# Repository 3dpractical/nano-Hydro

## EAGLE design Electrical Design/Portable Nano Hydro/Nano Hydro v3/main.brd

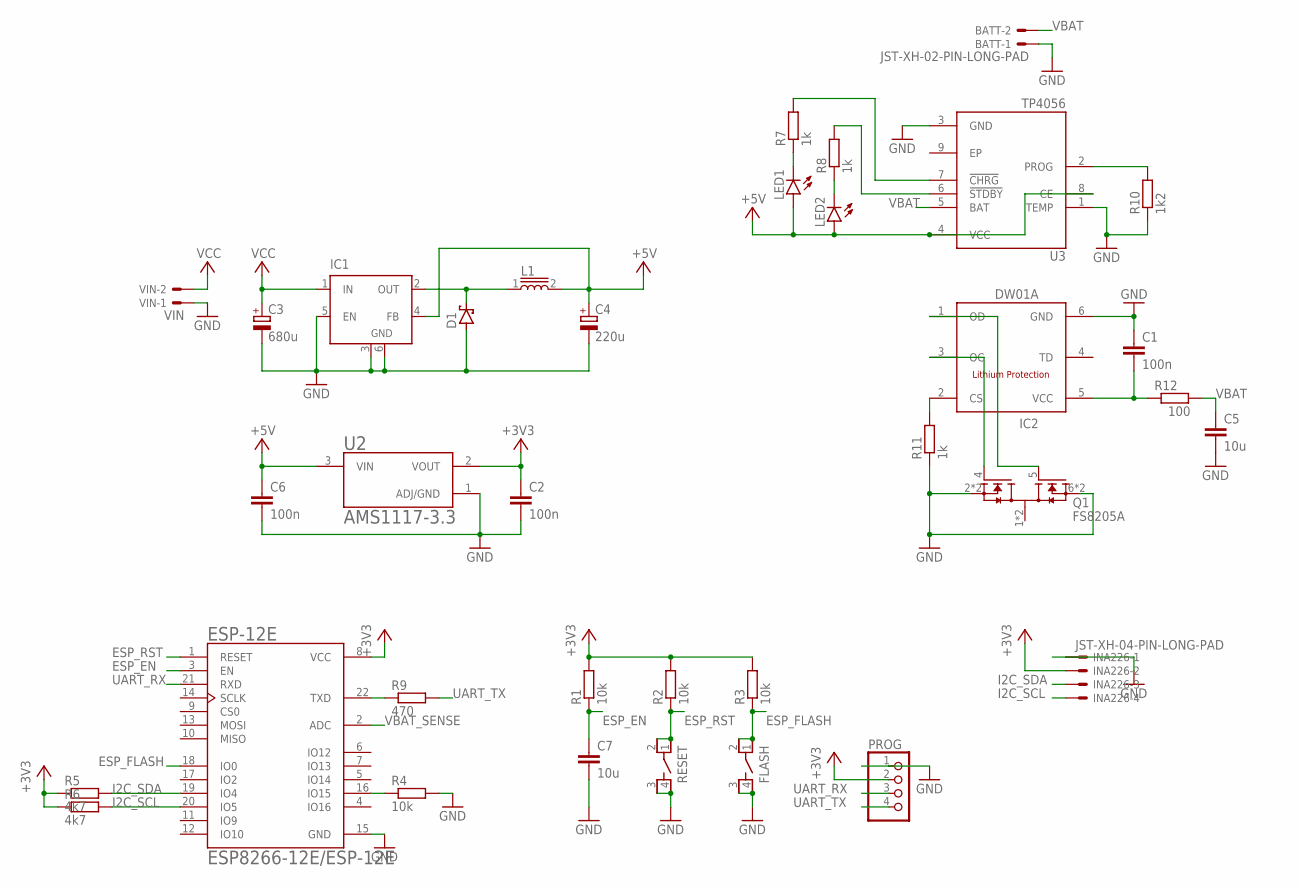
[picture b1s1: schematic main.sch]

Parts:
BATT: JST-XH-02-PIN-LONG-PAD; JST-XH-02-PACKAGE-LONG-PAD
C1, C2, C6: 100n; C0805
C3: 680u; 150CLZ-1010
C4: 220u; 150CLZ-0810
C5, C7: 10u; C0805
D1: SCHOTTKY-DIODESMD; SMB
ESP-12E: ESP8266-12E/ESP-12E; XCVR_ESP8266-12E/ESP-12E
FLASH: PTS810_SJM_250_SMTR_LFS; SW_PTS810_SJM_250_SMTR_LFS
IC1: LM2596S; TO263-5
IC2: DW01A; SOT23-6
INA226: JST-XH-04-PIN-LONG-PAD; JST-XH-04-PACKAGE-LONG-PAD
L1: 33uH; INDM1250X1250X600
LED1, LED2: LEDCHIPLED_0805; CHIPLED_0805
PROG: PINHD-1X4; 1X04
Q1: FS8205A; SOP65P640X120-8N
R1, R2, R3, R4: 10k; R0805
R5, R6: 4k7; R0805
R7, R8, R11: 1k; R0805
R9: 470; R0805
R10: 1k2; R0805
R12: 100; R0805
RESET: PTS810_SJM_250_SMTR_LFS; SW_PTS810_SJM_250_SMTR_LFS
U2: AMS1117-3.3; SOT229P700X180-4N
U3: TP4056; SOP127P600X175-9N
VIN: VIN; JST-XH-02-PACKAGE-LONG-PAD

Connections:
+3V3: C2.1, ESP-12E.8 (VCC), INA226.2, PROG.2, R1.2, R2.2, R3.2, R5.1, R6.1, U2.2 (VOUT)
+5V: C4.+, C6.1, IC1.4 (FB), L1.2, LED1.A, LED2.A, U2.3 (VIN), U3.4 (VCC), U3.8 (CE)
ESP_EN: C7.1, ESP-12E.3 (EN), R1.1
ESP_FLASH: ESP-12E.18 (IO0), FLASH.1, FLASH.2, R3.1
ESP_RST: ESP-12E.1 (RESET), R2.1, RESET.1, RESET.2
GND: BATT.1, C1.1, C2.2, C3.-, C4.-, C5.2, C6.2, C7.2, D1.A, ESP-12E.15 (GND), FLASH.3, FLASH.4, IC1.3 (GND), IC1.5 (EN), IC1.6 (GND), IC2.6 (GND), INA226.1, PROG.1, Q1.2 (S1), Q1.3 (S1), Q1.6 (S2), Q1.7 (S2), R4.2, R10.1, R11.1, RESET.3, RESET.4, U2.1 (ADJ/GND), U3.1 (TEMP), U3.3 (GND), VIN.1
I2C_SCL: ESP-12E.20 (IO5), INA226.4, R6.2
I2C_SDA: ESP-12E.19 (IO4), INA226.3, R5.2
unnamed: ESP-12E.22 (TXD), R9.1
unnamed: ESP-12E.16 (IO15), R4.1
unnamed: LED1.C, R7.1
unnamed: LED2.C, R8.1
unnamed: D1.C, IC1.2 (OUT), L1.1
unnamed: R8.2, U3.6 (!STDBY)
unnamed: R7.2, U3.7 (!CHRG)
unnamed: R10.2, U3.2 (PROG)
unnamed: IC2.2 (CS), R11.2
unnamed: C1.2, IC2.5 (VCC), R12.1
unnamed: IC2.3 (OC), Q1.4 (G1)
unnamed: IC2.1 (OD), Q1.5 (G2)
UART_RX: ESP-12E.21 (RXD), PROG.3
UART_TX: PROG.4, R9.2
VBAT: BATT.2, C5.1, R12.2, U3.5 (BAT)
VBAT_SENSE: ESP-12E.2 (ADC)
VCC: C3.+, IC1.1 (IN), VIN.2

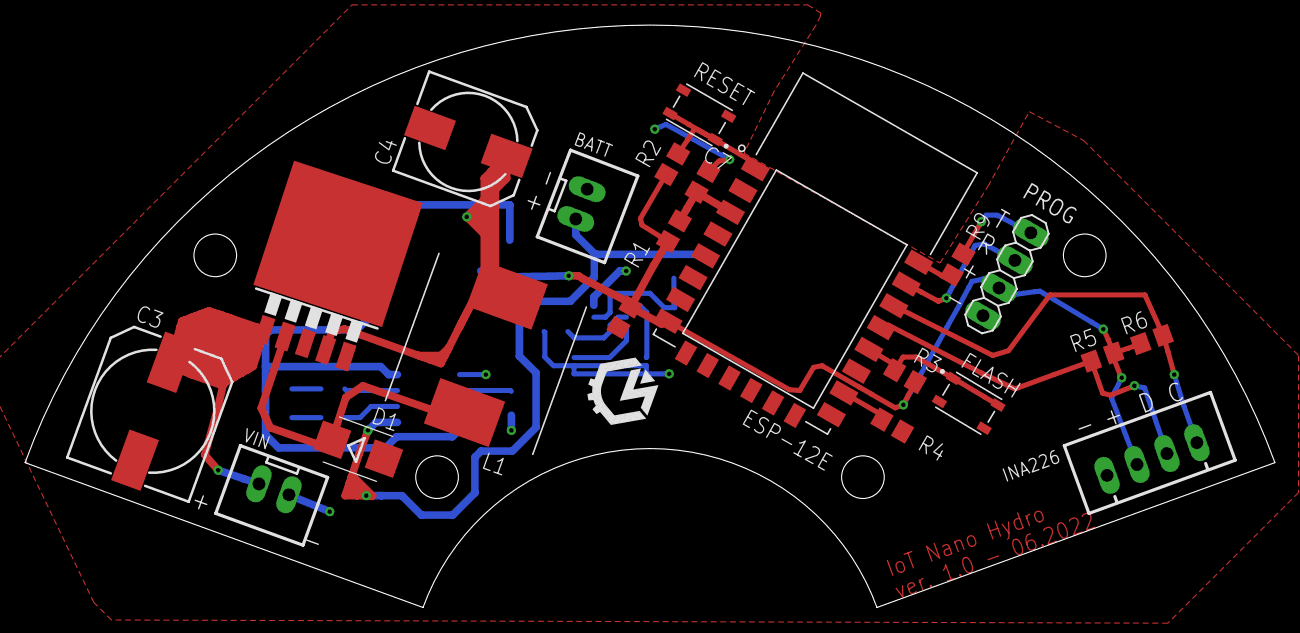
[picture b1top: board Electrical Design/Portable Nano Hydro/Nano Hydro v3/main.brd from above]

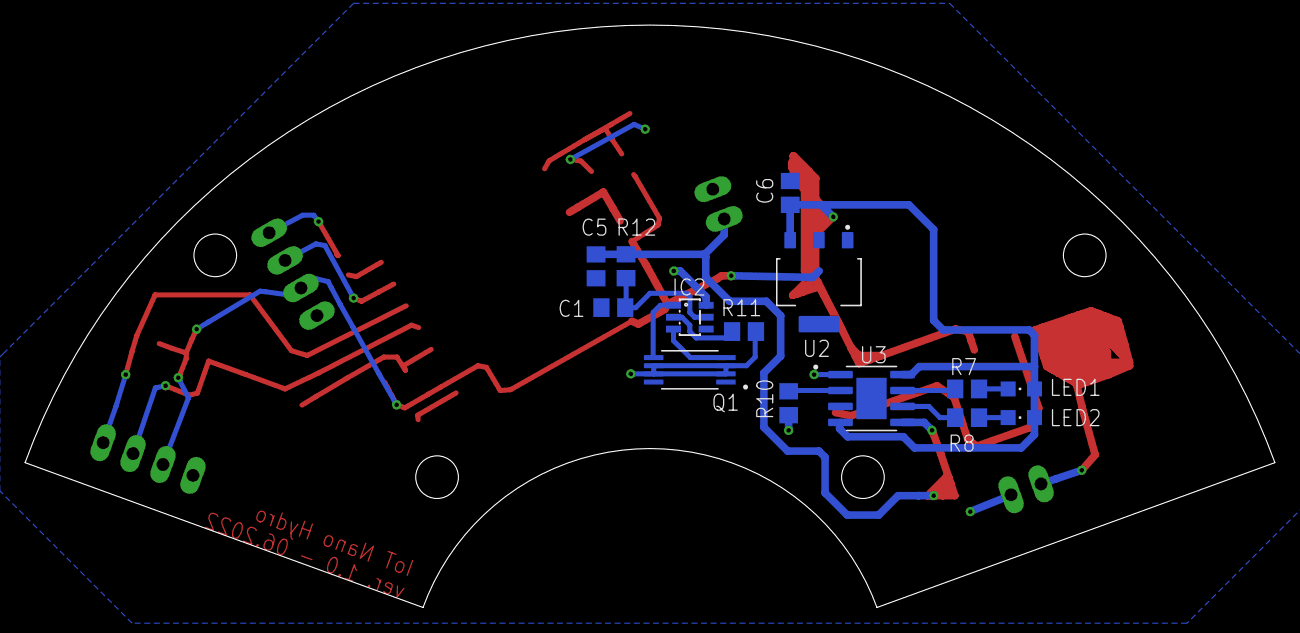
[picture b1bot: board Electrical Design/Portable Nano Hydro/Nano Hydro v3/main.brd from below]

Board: 2 copper layers, 99.6 x 46.4 mm, 35 parts (14 on the bottom side), 24 nets.

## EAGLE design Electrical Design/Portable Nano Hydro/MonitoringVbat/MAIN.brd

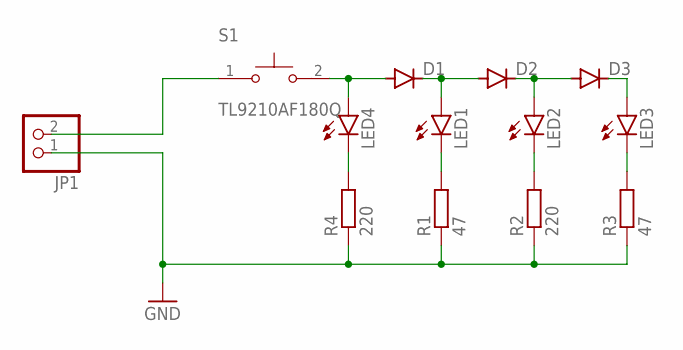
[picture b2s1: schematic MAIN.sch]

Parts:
D1, D2, D3: DIODE-SMB; SMB
JP1: PINHD-1X2; 1X02
LED1, LED2, LED3, LED4: LED5MM
R1, R3: 47; R0805
R2, R4: 220; R0805
S1: TL9210AF180Q; SW_TL9210AF180Q

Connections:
GND: JP1.1, R1.1, R2.1, R3.1, R4.1
unnamed: D1.C, D2.A, LED1.A
unnamed: D2.C, D3.A, LED2.A
unnamed: D3.C, LED3.A
unnamed: D1.A, LED4.A, S1.2
unnamed: LED4.K (C), R4.2
unnamed: LED1.K (C), R1.2
unnamed: LED2.K (C), R2.2
unnamed: LED3.K (C), R3.2
unnamed: JP1.2, S1.1

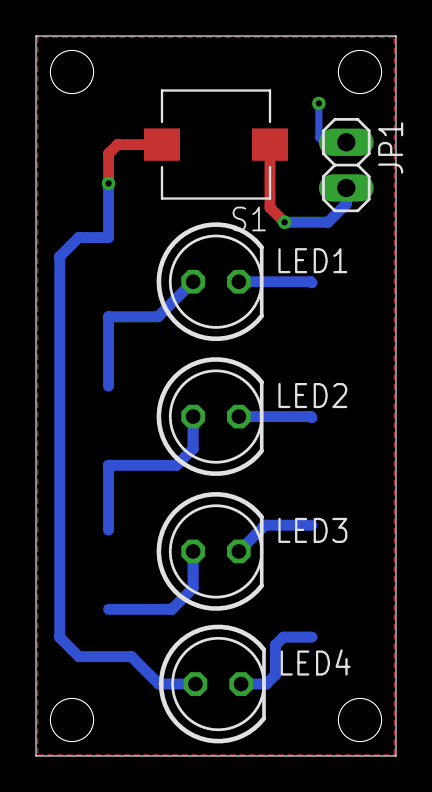
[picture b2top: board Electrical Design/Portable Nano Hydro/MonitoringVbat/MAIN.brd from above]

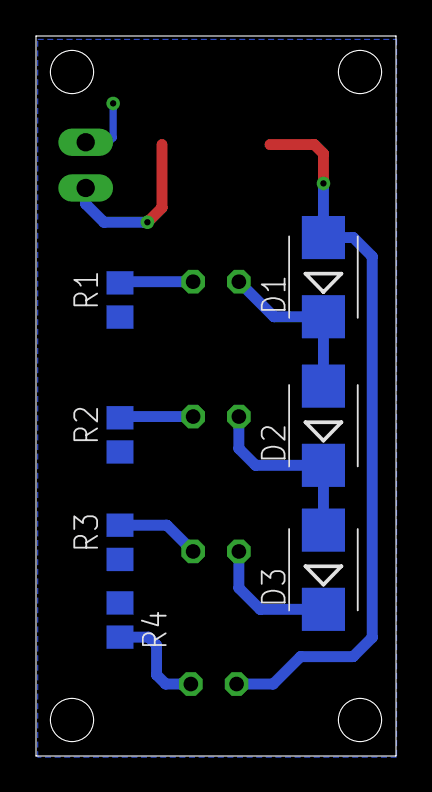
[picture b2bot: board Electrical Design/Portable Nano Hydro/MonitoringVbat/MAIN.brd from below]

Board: 2 copper layers, 20.0 x 40.0 mm, 13 parts (7 on the bottom side), 10 nets.

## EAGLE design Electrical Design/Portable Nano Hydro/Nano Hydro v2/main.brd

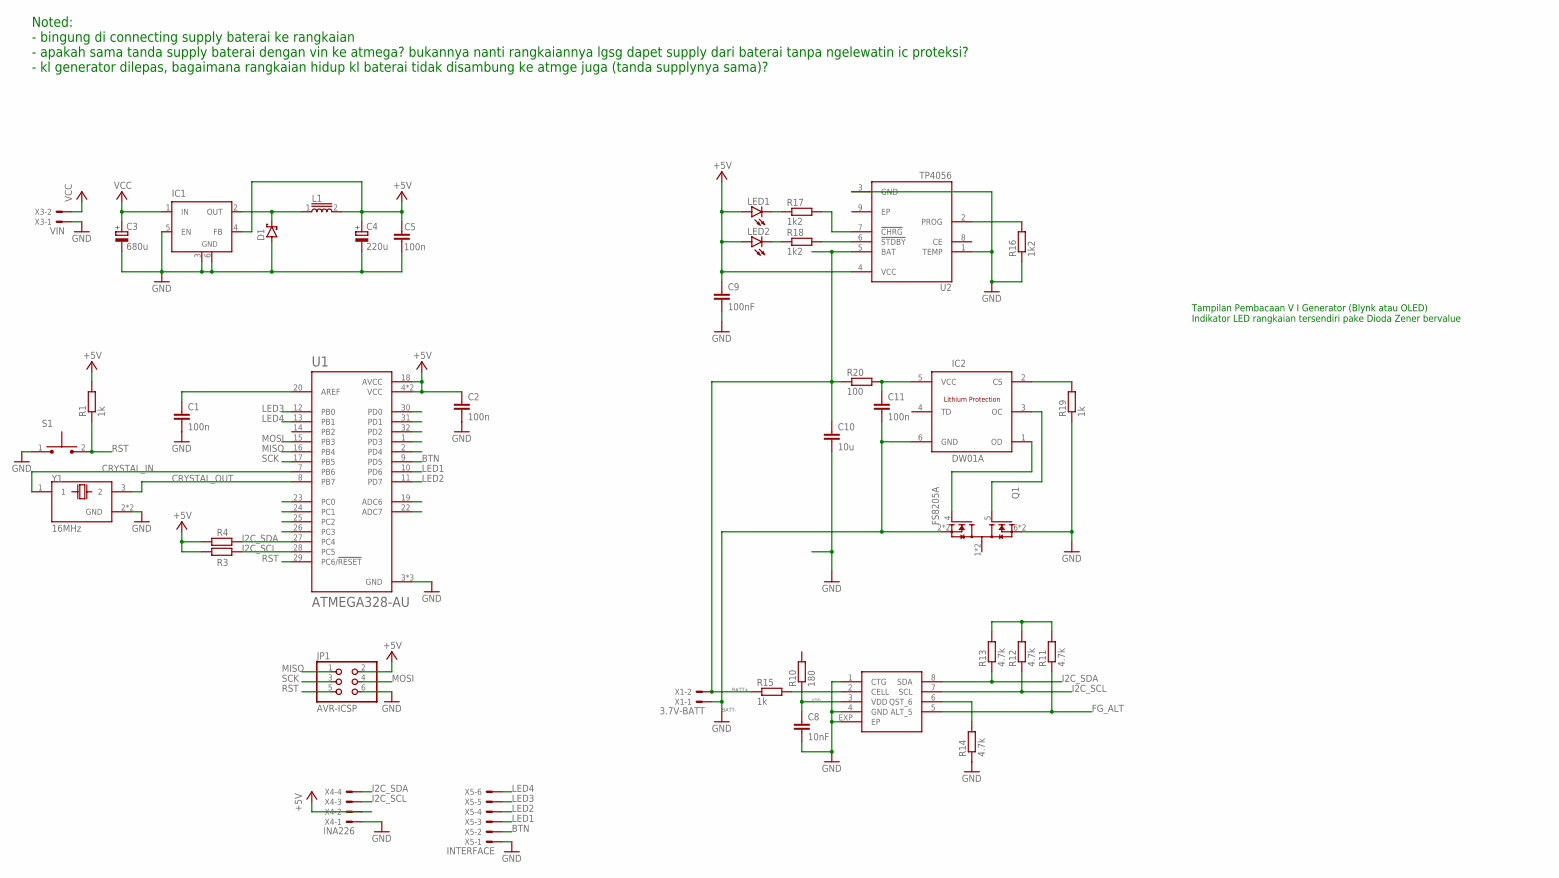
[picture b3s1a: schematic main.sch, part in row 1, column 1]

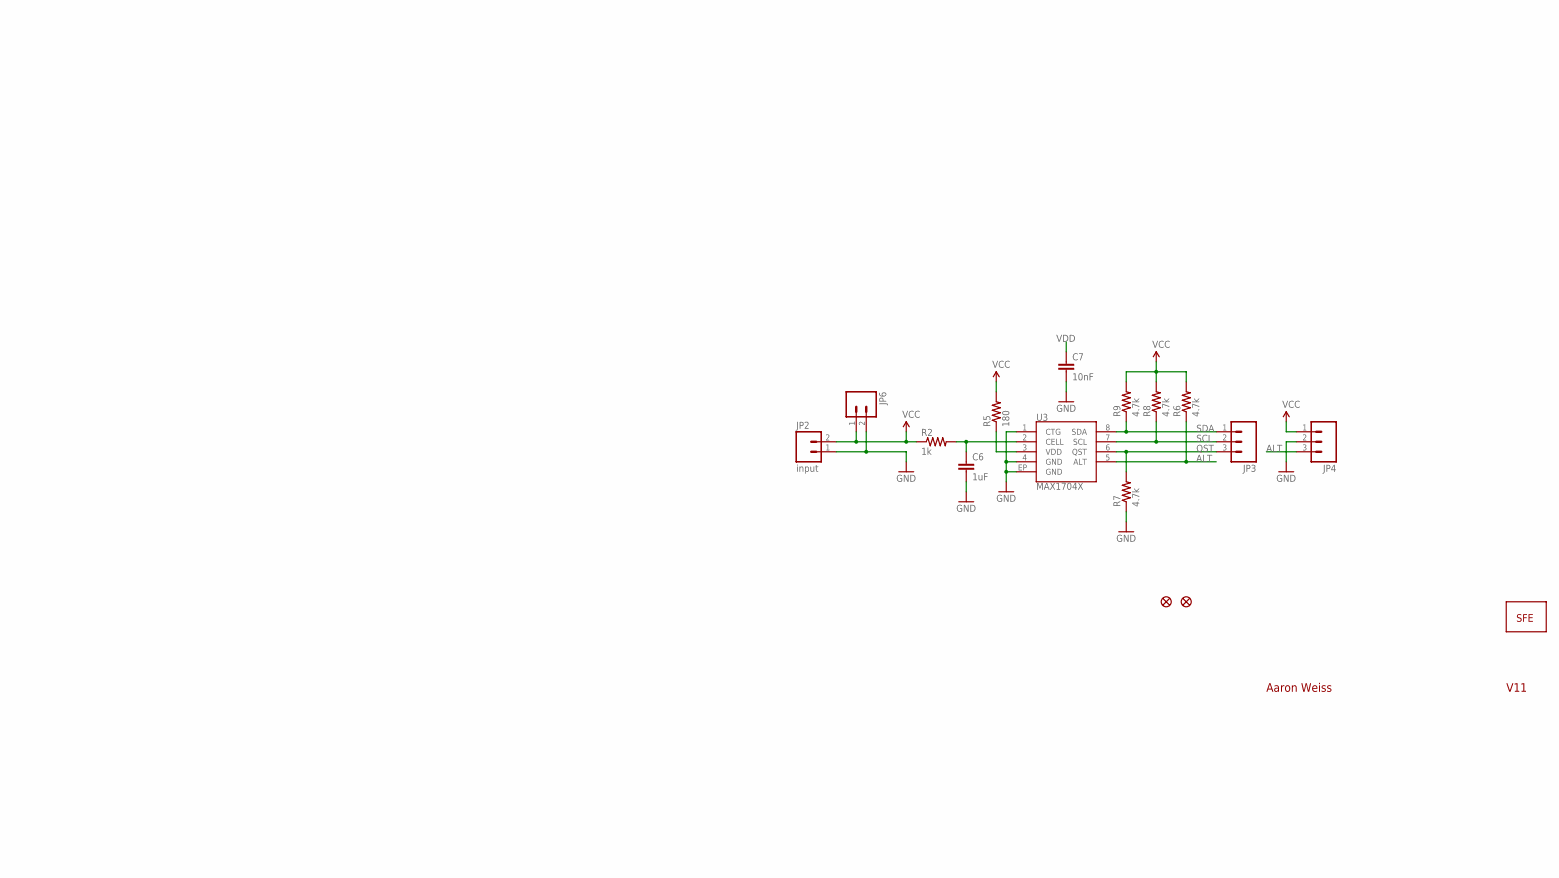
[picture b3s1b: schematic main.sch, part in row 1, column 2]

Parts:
C1, C2, C5: 100n; C0805
C3: 680u; 150CLZ-1010
C4: 220u; 150CLZ-0810
C6: 1uF; 0402-CAP
C7: 10nF; 0402-CAP
C8: 10nF; C0402
C9: 100nF; C0603
C10: 10u; C0603
C11: 100n; C0603
D1: SCHOTTKY-DIODESMD; SMB
IC1: LM2596S; TO263-5
IC2: DW01A; SOT23-6
JP1: AVR-ICSP; 2X03
JP2: input; JST-2-SMD
JP3, JP4: M03PTH; 1X03
JP5: LOGO-SFESK; SFE-LOGO-FLAME
JP6: M02PTH; 1X02
JP7, JP8: FIDUCIAL1X2.5; FIDUCIAL-1X2.5
L1: 33uH; INDM1250X1250X600
LED1, LED2: LEDCHIPLED_0603; CHIPLED_0603
Q1: FS8205A; SOP65P640X120-8N
R1: 1k; R0805
R2: 1k; 0402-RES
R3, R4: R-EU_R0805; R0805
R5: 180; 0402-RES
R6, R7, R8, R9: 4.7k; 0402-RES
R10: 180; R0402
R11, R12, R13, R14: 4.7k; R0402
R15: 1k; R0402
R16, R17, R18: 1k2; R0603
R19: 1k; R0603
R20: 100; R0603
S1: TL1015AF160QG; SW_TL1015AF160QG
U1: ATMEGA328-AU; QFP80P900X900X120-32N
U2: TP4056; SOP127P600X175-9N
U3: MAX1704X; TDFN-8
U$1: MAX17043; DFN-2X3
X1: 3.7V-BATT; JST-XH-02-PACKAGE-LONG-PAD
X3: VIN; JST-XH-02-PACKAGE-LONG-PAD
X4: INA226; JST-XH-04-PACKAGE-LONG-PAD
X5: INTERFACE; JST-XH-06-PACKAGE-LONG-PAD
Y1: 16MHz; XTAL_TSX-3225_16.0000MF18X-AC3

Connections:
+5V: C2.1, C4.+, C5.2, C9.1, IC1.4 (FB), JP1.2, L1.2, LED1.A, LED2.A, R1.2, R3.1, R4.1, U1.4 (VCC), U1.6 (VCC), U1.18 (AVCC), U2.4 (VCC), X4.2
ALT: JP4.3, R6.1, U3.5 (ALT)
BATT+: C10.1, R15.1, R20.1, U2.5 (BAT), X1.2
BATT-: C11.2, IC2.6 (GND), Q1.2 (S1), Q1.3 (S1), X1.1
BTN: U1.9 (PD5), X5.2
CRYSTAL_IN: U1.7 (PB6), Y1.1
CRYSTAL_OUT: U1.8 (PB7), Y1.3 (2)
FG_ALT: R11.1, U$1.5 (ALT_5)
FG_QST: R14.2, U$1.6 (QST_6)
GND: C1.2, C2.2, C3.-, C4.-, C5.1, C6.2, C7.2, C8.2, C9.2, C10.2, D1.A, IC1.3 (GND), IC1.5 (EN), IC1.6 (GND), JP1.6, JP2.1, JP4.2, JP6.2, Q1.6 (S2), Q1.7 (S2), R7.1, R14.1, R16.1, R19.1, S1.1, U1.3 (GND), U1.5 (GND), U1.21 (GND), U2.1 (TEMP), U2.3 (GND), U3.1 (CTG), U3.4 (GND), U3.EP (GND), U$1.1 (CTG), U$1.4 (GND), U$1.EXP (EP), X3.1, X4.1, X5.1, Y1.2 (GND), Y1.4 (GND)
I2C_SCL: R3.2, R12.1, U1.28 (PC5), U$1.7 (SCL), X4.3
I2C_SDA: R4.2, R13.1, U1.27 (PC4), U$1.8 (SDA), X4.4
LED1: U1.10 (PD6), X5.3
LED2: U1.11 (PD7), X5.4
LED3: U1.12 (PB0), X5.5
LED4: U1.13 (PB1), X5.6
MAX_ALT: U1.32 (PD2)
MISO: JP1.1, U1.16 (PB4)
MOSI: JP1.4, U1.15 (PB3)
unnamed: C1.1, U1.20 (AREF)
unnamed: C6.1, R2.2, U3.2 (CELL)
unnamed: D1.C, IC1.2 (OUT), L1.1
unnamed: R16.2, U2.2 (PROG)
unnamed: LED1.C, R17.1
unnamed: R15.2, U$1.2 (CELL)
unnamed: R17.2, U2.7 (!CHRG)
unnamed: R18.2, U2.6 (!STDBY)
unnamed: R11.2, R12.2, R13.2
unnamed: LED2.C, R18.1
unnamed: IC2.2 (CS), R19.2
unnamed: IC2.1 (OD), Q1.4 (G1)
unnamed: C11.1, IC2.5 (VCC), R20.2
unnamed: IC2.3 (OC), Q1.5 (G2)
QST: JP3.3, R7.2, U3.6 (QST)
RST: JP1.5, R1.1, S1.2, U1.29 (PC6/!RESET)
SCK: JP1.3, U1.17 (PB5)
SCL: JP3.2, R8.1, U3.7 (SCL)
SDA: JP3.1, R9.1, U3.8 (SDA)
VCC: C3.+, IC1.1 (IN), JP2.2, JP4.1, JP6.1, R2.1, R5.2, R6.2, R8.2, R9.2, X3.2
VDD: C7.1, C8.1, R5.1, R10.1, U3.3 (VDD), U$1.3 (VDD)

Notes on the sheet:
V11
Aaron Weiss
Noted: - bingung di connecting supply baterai ke rangkaian - apakah sama tanda supply baterai dengan vin ke atmega? bukannya nanti rangkaiannya lgsg dapet supply dari baterai tanpa ngelewatin ic proteksi? - kl generator dilepas, bagaimana rangkaian hidup kl baterai tidak disambung ke atmge juga (ta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
Tampilan Pembacaan V I Generator (Blynk atau OLED) Indikator LED rangkaian tersendiri pake Dioda Zener bervalue

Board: 2 copper layers, 56 parts (0 on the bottom side), 39 nets, no tracks yet.

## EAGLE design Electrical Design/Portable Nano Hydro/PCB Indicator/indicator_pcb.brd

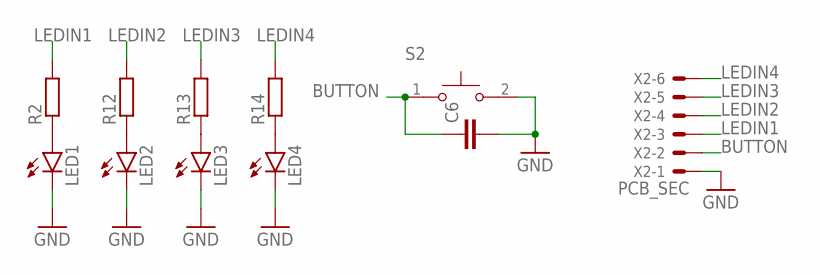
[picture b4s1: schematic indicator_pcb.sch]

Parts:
C6: C-EUC0603; C0603
LED1, LED2, LED3, LED4: LEDCHIP-LED0805; CHIP-LED0805
R2, R12, R13, R14: R-EU_R0805; R0805
S2: TL9210AF180Q; SW_TL9210AF180Q
X2: PCB_SEC; JST-XH-06-PACKAGE-LONG-PAD

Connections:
BUTTON: C6.1, S2.1, X2.2
GND: C6.2, LED1.C, LED2.C, LED3.C, LED4.C, S2.2, X2.1
LEDIN1: R2.2, X2.3
LEDIN2: R12.2, X2.4
LEDIN3: R13.2, X2.5
LEDIN4: R14.2, X2.6
unnamed: LED1.A, R2.1
unnamed: LED2.A, R12.1
unnamed: LED3.A, R13.1
unnamed: LED4.A, R14.1

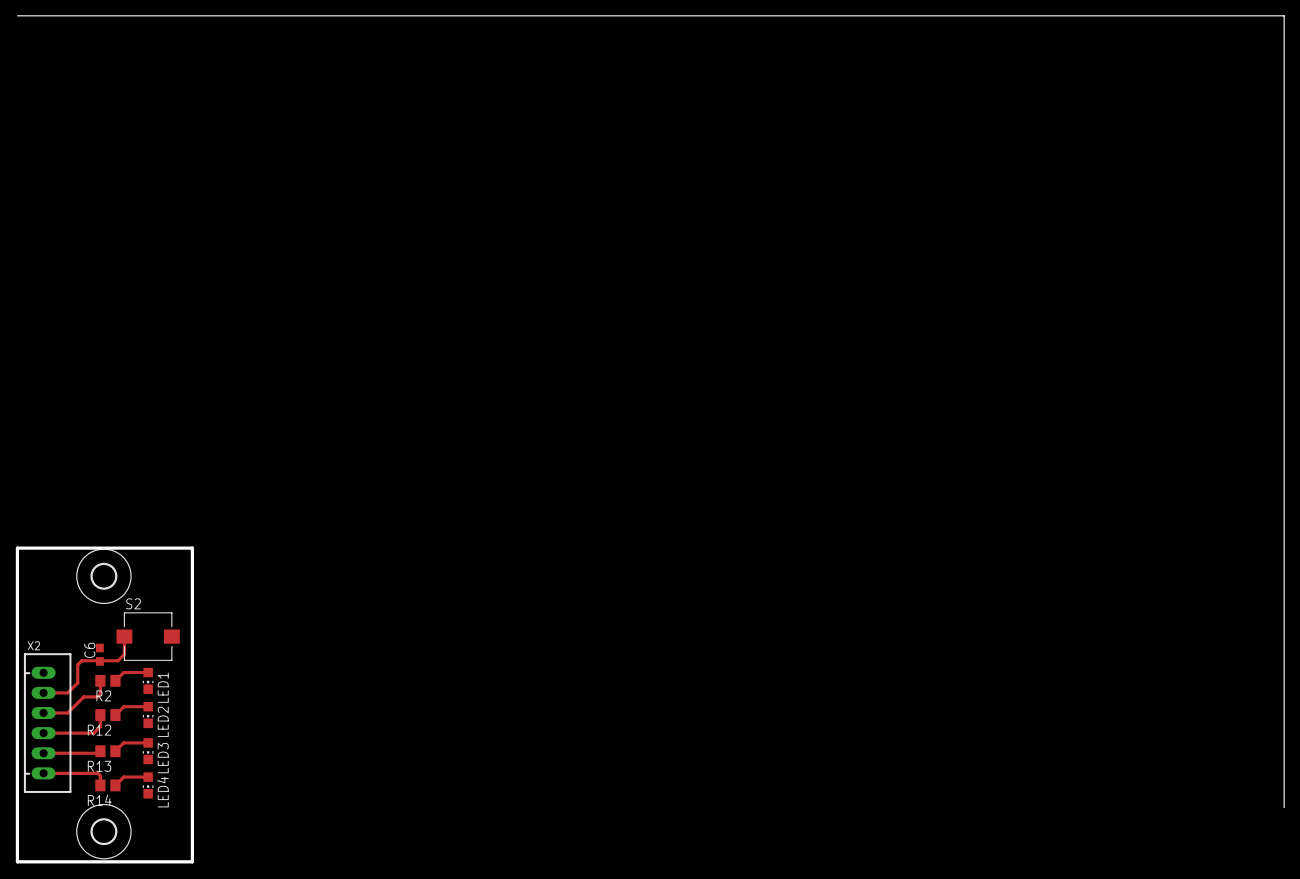
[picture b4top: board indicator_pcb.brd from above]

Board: 2 copper layers, 22.1 x 39.6 mm, 13 parts (0 on the bottom side), 10 nets.

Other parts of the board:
U$1, U$2: 3,0
